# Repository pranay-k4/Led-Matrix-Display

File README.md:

# Led-Matrix-Display
This is a custom Smart LED matrix display system built using ESP32 and HUB75 RGB matrix. Its has many modes like clock, text, animation which can be controlled by the user.

## Features
- Real time Clock display
- Multiple display modes
- Button based control
- RTC timekeeping

## System design
See detailed system design in ' docs/architecture.md '.

## Hardware Components
- ESP32 Devboard
- HUB75 RGB matrix
- RTC module
- Buttons
- Custom PCB

## Status
In designing phase.

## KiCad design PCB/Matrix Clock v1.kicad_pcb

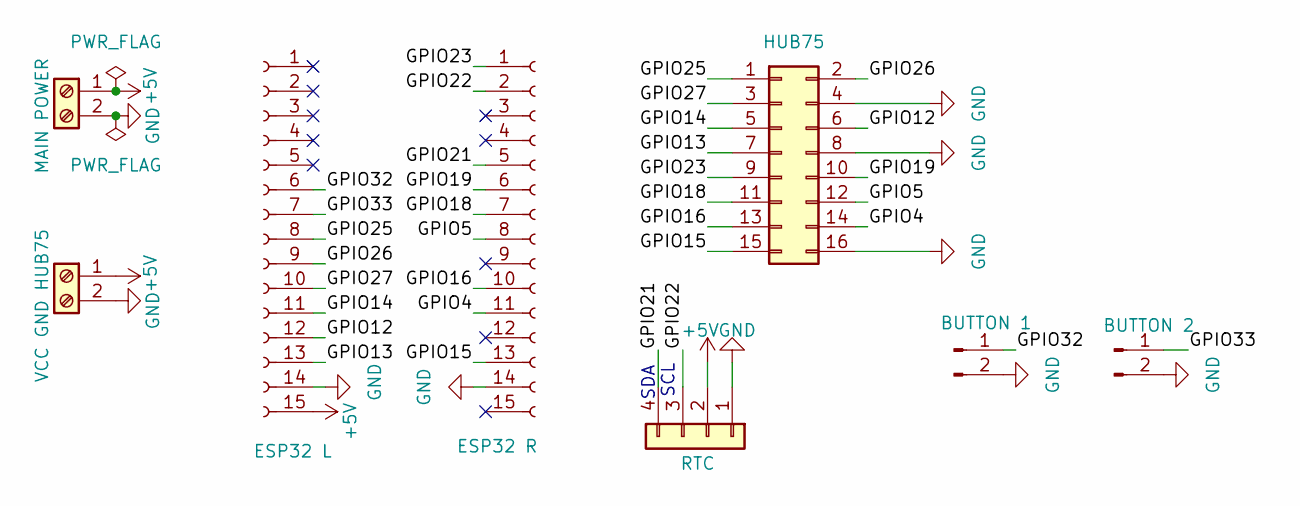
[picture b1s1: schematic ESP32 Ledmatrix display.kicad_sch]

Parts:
J1: HUB75; PinHeader_2x08_P2.54mm_Vertical
J2: RTC; PinHeader_1x04_P2.54mm_Vertical
J3: ESP32 R; PinSocket_1x15_P2.54mm_Vertical
J4: ESP32 L; PinSocket_1x15_P2.54mm_Vertical
J5: MAIN POWER; TerminalBlock_Phoenix_MKDS-1,5-2-5.08_1x02_P5.08mm_Horizont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
J6: VCC GND HUB75; TerminalBlock_Phoenix_MKDS-1,5-2-5.08_1x02_P5.08mm_Horizont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
J7: BUTTON 1; PinHeader_1x02_P2.54mm_Vertical
J8: BUTTON 2; PinHeader_1x02_P2.54mm_Vertical

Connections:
+5V: J2.2, J4.15, J5.1, J6.1
/GPIO4: J1.14, J3.11
/GPIO5: J1.12, J3.8
/GPIO12: J1.6, J4.12
/GPIO13: J1.7, J4.13
/GPIO14: J1.5, J4.11
/GPIO15: J1.15, J3.13
/GPIO16: J1.13, J3.10
/GPIO18: J1.11, J3.7
/GPIO19: J1.10, J3.6
/GPIO21: J2.4, J3.5
/GPIO22: J2.3, J3.2
/GPIO23: J1.9, J3.1
/GPIO25: J1.1, J4.8
/GPIO26: J1.2, J4.9
/GPIO27: J1.3, J4.10
/GPIO32: J4.6, J7.1
/GPIO33: J4.7, J8.1
GND: J1.4, J1.8, J1.16, J2.1, J3.14, J4.14, J5.2, J6.2, J7.2, J8.2

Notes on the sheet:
SDA
SCL

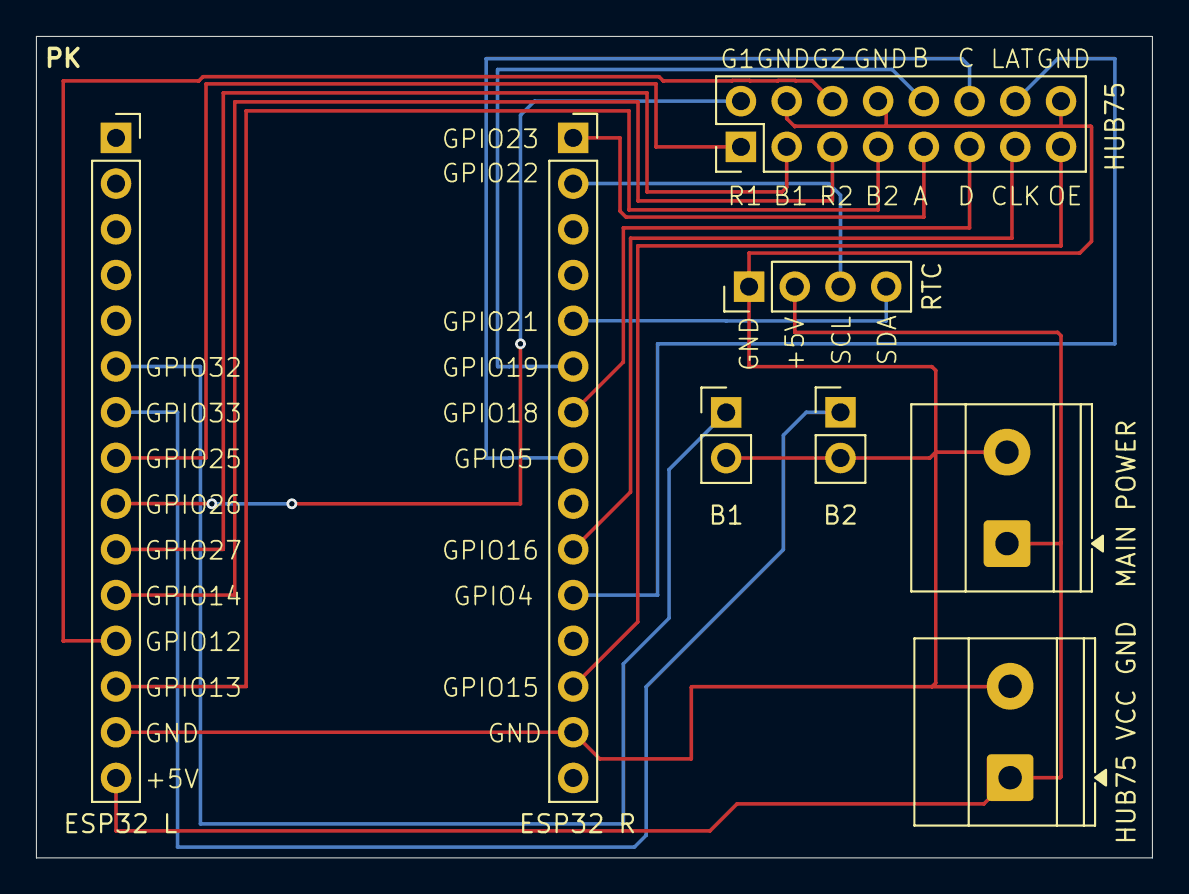
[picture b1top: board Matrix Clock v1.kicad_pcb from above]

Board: 2 copper layers, 62.0 x 45.6 mm, 8 parts (0 on the bottom side), 19 nets.

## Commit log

2026-04-25 Create a
2026-05-02 Create LICENSE
2026-05-10 Rename docs/BOM.md to BOM.md
2026-05-10 Rename ESP32 Ledmatrix display.kicad_sch to ESP32 Ledmatrix display.kicad_sch
2026-05-17 Rename Matrix Clock v1.step to CAD/Matrix Clock v1.step
2026-05-17 Rename ESP32 Ledmatrix display.kicad_pcb to ESP32 Ledmatrix display.kicad_pcb
2026-05-17 Rename hardware/ESP32 Ledmatrix display.kicad_sch to Matrix Clock v1.kicad_sch
2026-05-17 Rename PCBGerbers.zip to PCB/Gerbers.zip
2026-05-17 Rename Matrix Clock v1.kicad_sch to PCB/Matrix Clock v1.kicad_sch
2026-05-17 Rename ESP32 Ledmatrix display.kicad_pcb to Matrix Clock v1.kicad_pcb
